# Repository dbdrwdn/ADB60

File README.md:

# ADB60

A modified [donegal-c](https://github.com/piit79/donegal-c).

This PCB allows to use the keycaps of an alphanumerical block of the Apple ADB keyboard as 60% keyboard.
It is designed to be used without any case.

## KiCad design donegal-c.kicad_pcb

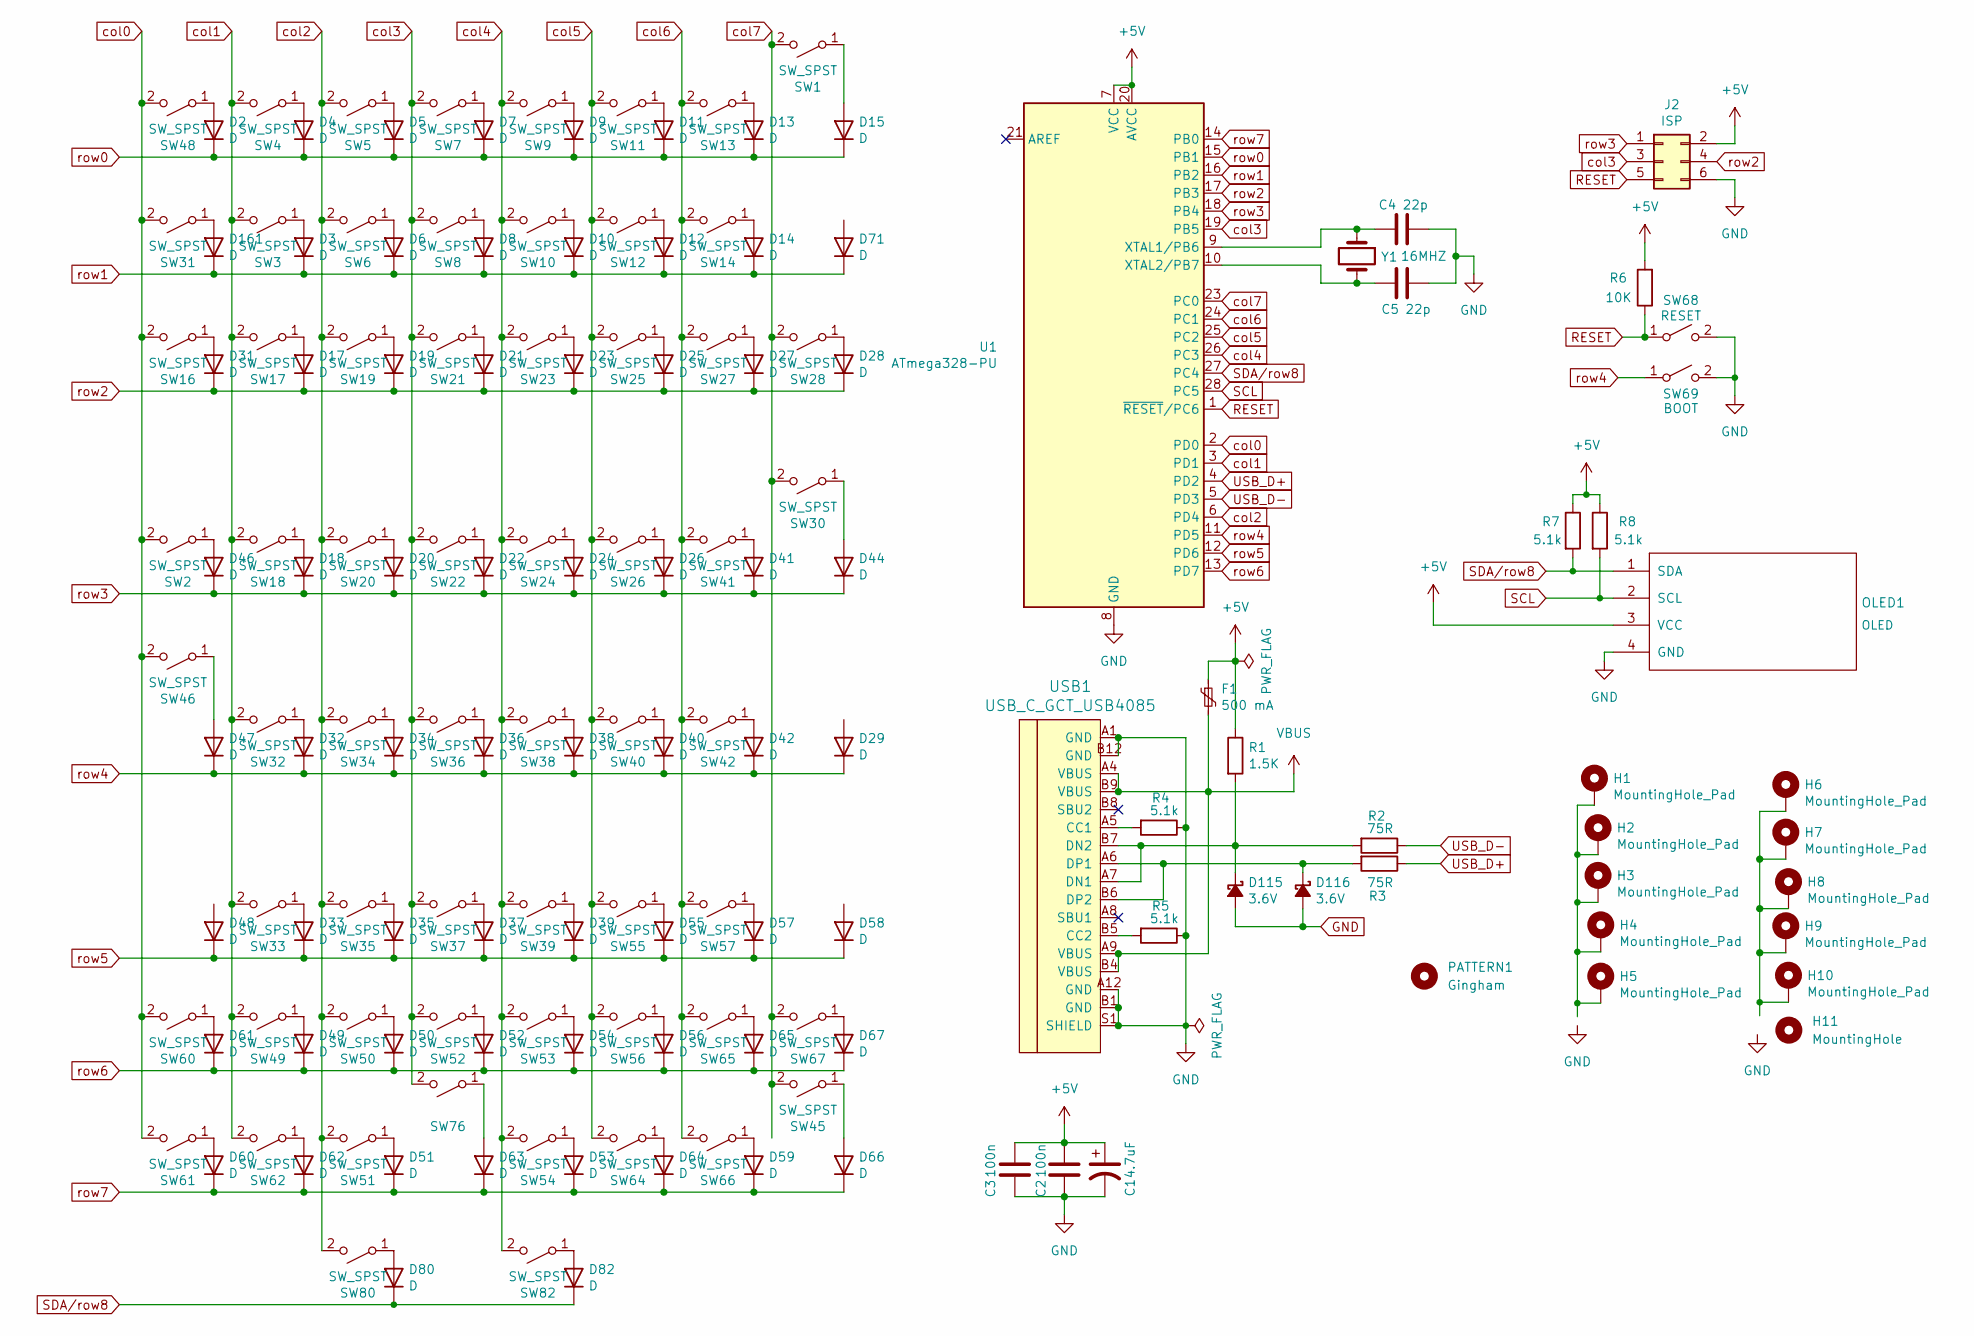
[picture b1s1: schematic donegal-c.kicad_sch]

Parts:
C1: 4.7uF; CP_Radial_D4.0mm_P1.50mm
C2, C3: 100n; C_Disc_D4.3mm_W1.9mm_P5.00mm
C4, C5: 22p; C_Disc_D3.0mm_W1.6mm_P2.50mm
D2, D3, D4, D5, D6, D7, D8, D9, D10, D11, D12, D13, D14, D15, D17, D18, D19, D20, D21, D22, D23, D24, D25, D26, D27, D28, D29, D31, D32, D33, D34, D35, D36, D37, D38, D39, D40, D41, D42, D44, D46, D47, D48, D49, D50, D51, D52, D53, D54, D55, D56, D57, D58, D59, D60, D61, D62, D63, D64, D65, D66, D67, D71, D80, D82, D161: D; D_DO-35_SOD27_P7.62mm_Horizontal
D115, D116: 3.6V; D_DO-35_SOD27_P7.62mm_Horizontal
F1: 500 mA; C_Disc_D5.0mm_W2.5mm_P5.00mm
H1, H2: MountingHole_Pad; MountingHole_2.2mm_M2
H3, H4, H6, H7, H8, H9, H10: MountingHole_Pad; MountingHole_2.2mm_M2_DIN965_Pad
H5: MountingHole_Pad; MountingHole_2.2mm_M2_DIN965
H11: MountingHole; MountingHole_2.2mm_M2
J2: ISP; PinHeader_2x03_P2.54mm_Vertical
OLED1: OLED; OLED_v2.1
PATTERN1: Gingham; gingham
R1: 1.5K; R_Axial_DIN0204_L3.6mm_D1.6mm_P5.08mm_Horizontal
R2, R3: 75R; R_Axial_DIN0204_L3.6mm_D1.6mm_P5.08mm_Horizontal
R4, R5, R7, R8: 5.1k; R_Axial_DIN0204_L3.6mm_D1.6mm_P5.08mm_Horizontal
R6: 10K; R_Axial_DIN0204_L3.6mm_D1.6mm_P5.08mm_Horizontal
SW1, SW16: SW_SPST; ALPS-1.5U
SW2, SW3, SW4, SW5, SW6, SW7, SW8, SW9, SW10, SW11, SW12, SW13, SW14, SW17, SW18, SW19, SW20, SW21, SW22, SW23, SW24, SW25, SW26, SW27, SW28, SW32, SW33, SW34, SW35, SW36, SW37, SW38, SW39, SW40, SW41, SW42, SW48, SW49, SW50, SW51, SW52, SW53, SW54, SW55, SW56, SW57, SW60, SW61, SW64, SW65, SW66, SW67, SW80, SW82: SW_SPST; ALPS-1U
SW30: SW_SPST; ALPS-2U
SW31, SW62: SW_SPST; ALPS-1.75U
SW45, SW46: SW_SPST; ALPS-2.25U
SW68: RESET; SW_PUSH_6mm
SW69: BOOT; SW_PUSH_6mm
SW76: (no value)
U1: ATmega328-PU; DIP-28_W7.62mm
USB1: USB_C_GCT_USB4085; USB_C_GCT_USB4085-offset-pads
Y1: 16MHZ; Crystal_HC49-4H_Vertical

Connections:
+5V: C1.1, C2.1, C3.1, F1.1, J2.2, OLED1.3 (VCC), R1.1, R6.2, R7.1, R8.1, U1.7 (VCC), U1.20 (AVCC)
GND: C1.2, C2.2, C3.2, C4.1, C5.1, D115.2 (A), D116.2 (A), J2.6, OLED1.4 (GND), R4.1, R5.1, SW68.2 (B), SW69.2 (B), U1.8 (GND), U1.22 (GND), USB1.A1 (GND), USB1.A12 (GND), USB1.B1 (GND), USB1.B12 (GND), USB1.S1 (SHIELD)
unnamed: C4.2, U1.9 (XTAL1/PB6), Y1.1
unnamed: C5.2, U1.10 (XTAL2/PB7), Y1.2
unnamed: D2.2 (A), SW48.1 (A)
unnamed: D3.2 (A), SW3.1 (A)
unnamed: D4.2 (A), SW4.1 (A)
unnamed: D5.2 (A), SW5.1 (A)
unnamed: D6.2 (A), SW6.1 (A)
unnamed: D7.2 (A), SW7.1 (A)
unnamed: D8.2 (A), SW8.1 (A)
unnamed: D9.2 (A), SW9.1 (A)
unnamed: D10.2 (A), SW10.1 (A)
unnamed: D11.2 (A), SW11.1 (A)
unnamed: D12.2 (A), SW12.1 (A)
unnamed: D13.2 (A), SW13.1 (A)
unnamed: D14.2 (A), SW14.1 (A)
unnamed: D15.2 (A), SW1.1 (A)
unnamed: D17.2 (A), SW17.1 (A)
unnamed: D18.2 (A), SW18.1 (A)
unnamed: D19.2 (A), SW19.1 (A)
unnamed: D20.2 (A), SW20.1 (A)
unnamed: D21.2 (A), SW21.1 (A)
unnamed: D22.2 (A), SW22.1 (A)
unnamed: D23.2 (A), SW23.1 (A)
unnamed: D24.2 (A), SW24.1 (A)
unnamed: D25.2 (A), SW25.1 (A)
unnamed: D26.2 (A), SW26.1 (A)
unnamed: D27.2 (A), SW27.1 (A)
unnamed: D28.2 (A), SW28.1 (A)
unnamed: D31.2 (A), SW16.1 (A)
unnamed: D32.2 (A), SW32.1 (A)
unnamed: D33.2 (A), SW33.1 (A)
unnamed: D34.2 (A), SW34.1 (A)
unnamed: D35.2 (A), SW35.1 (A)
unnamed: D36.2 (A), SW36.1 (A)
unnamed: D37.2 (A), SW37.1 (A)
unnamed: D38.2 (A), SW38.1 (A)
unnamed: D39.2 (A), SW39.1 (A)
unnamed: D40.2 (A), SW40.1 (A)
unnamed: D41.2 (A), SW41.1 (A)
unnamed: D42.2 (A), SW42.1 (A)
unnamed: D44.2 (A), SW30.1 (A)
unnamed: D46.2 (A), SW2.1 (A)
unnamed: D47.2 (A), SW46.1 (A)
unnamed: D49.2 (A), SW49.1 (A)
unnamed: D50.2 (A), SW50.1 (A)
unnamed: D51.2 (A), SW51.1 (A)
unnamed: D52.2 (A), SW52.1 (A)
unnamed: D53.2 (A), SW54.1 (A)
unnamed: D54.2 (A), SW53.1 (A)
unnamed: D55.2 (A), SW55.1 (A)
unnamed: D56.2 (A), SW56.1 (A)
unnamed: D57.2 (A), SW57.1 (A)
unnamed: D59.2 (A), SW66.1 (A)
unnamed: D60.2 (A), SW61.1 (A)
unnamed: D61.2 (A), SW60.1 (A)
unnamed: D62.2 (A), SW62.1 (A)
unnamed: D63.2 (A), SW76.1 (A)
unnamed: D64.2 (A), SW64.1 (A)
unnamed: D65.2 (A), SW65.1 (A)
unnamed: D66.2 (A), SW45.1 (A)
unnamed: D67.2 (A), SW67.1 (A)
unnamed: D80.2 (A), SW80.1 (A)
unnamed: D82.2 (A), SW82.1 (A)
unnamed: D115.1 (K), R1.2, R2.2, USB1.A7 (DN1), USB1.B7 (DN2)
unnamed: D116.1 (K), R3.2, USB1.A6 (DP1), USB1.B6 (DP2)
unnamed: D161.2 (A), SW31.1 (A)
unnamed: H1.1, H2.1, H3.1, H4.1, H5.1
unnamed: H6.1, H7.1, H8.1, H9.1, H10.1
unnamed: R4.2, USB1.A5 (CC1)
unnamed: R5.2, USB1.B5 (CC2)
RESET: J2.5, R6.1, SW68.1 (A), U1.1 (~RESET/PC6)
SCL: OLED1.2 (SCL), R8.2, U1.28 (PC5)
SDA/row8: D80.1 (K), D82.1 (K), OLED1.1 (SDA), R7.2, U1.27 (PC4)
USB_D+: R3.1, U1.4 (PD2)
USB_D-: R2.1, U1.5 (PD3)
VBUS: F1.2, USB1.A4 (VBUS), USB1.A9 (VBUS), USB1.B4 (VBUS), USB1.B9 (VBUS)
col0: SW2.2 (B), SW16.2 (B), SW31.2 (B), SW46.2 (B), SW48.2 (B), SW60.2 (B), SW61.2 (B), U1.2 (PD0)
col1: SW3.2 (B), SW4.2 (B), SW17.2 (B), SW18.2 (B), SW32.2 (B), SW33.2 (B), SW49.2 (B), SW62.2 (B), U1.3 (PD1)
col2: SW5.2 (B), SW6.2 (B), SW19.2 (B), SW20.2 (B), SW34.2 (B), SW35.2 (B), SW50.2 (B), SW51.2 (B), SW80.2 (B), U1.6 (PD4)
col3: J2.3, SW7.2 (B), SW8.2 (B), SW21.2 (B), SW22.2 (B), SW36.2 (B), SW37.2 (B), SW52.2 (B), SW76.2 (B), U1.19 (PB5)
col4: SW9.2 (B), SW10.2 (B), SW23.2 (B), SW24.2 (B), SW38.2 (B), SW39.2 (B), SW53.2 (B), SW54.2 (B), SW82.2 (B), U1.26 (PC3)
col5: SW11.2 (B), SW12.2 (B), SW25.2 (B), SW26.2 (B), SW40.2 (B), SW55.2 (B), SW56.2 (B), SW64.2 (B), U1.25 (PC2)
col6: SW13.2 (B), SW14.2 (B), SW27.2 (B), SW41.2 (B), SW42.2 (B), SW57.2 (B), SW65.2 (B), SW66.2 (B), U1.24 (PC1)
col7: SW1.2 (B), SW28.2 (B), SW30.2 (B), SW45.2 (B), SW67.2 (B), U1.23 (PC0)
row0: D2.1 (K), D4.1 (K), D5.1 (K), D7.1 (K), D9.1 (K), D11.1 (K), D13.1 (K), D15.1 (K), U1.15 (PB1)
row1: D3.1 (K), D6.1 (K), D8.1 (K), D10.1 (K), D12.1 (K), D14.1 (K), D71.1 (K), D161.1 (K), U1.16 (PB2)
row2: D17.1 (K), D19.1 (K), D21.1 (K), D23.1 (K), D25.1 (K), D27.1 (K), D28.1 (K), D31.1 (K), J2.4, U1.17 (PB3)
row3: D18.1 (K), D20.1 (K), D22.1 (K), D24.1 (K), D26.1 (K), D41.1 (K), D44.1 (K), D46.1 (K), J2.1, U1.18 (PB4)
row4: D29.1 (K), D32.1 (K), D34.1 (K), D36.1 (K), D38.1 (K), D40.1 (K), D42.1 (K), D47.1 (K), SW69.1 (A), U1.11 (PD5)
row5: D33.1 (K), D35.1 (K), D37.1 (K), D39.1 (K), D48.1 (K), D55.1 (K), D57.1 (K), D58.1 (K), U1.12 (PD6)
row6: D49.1 (K), D50.1 (K), D52.1 (K), D54.1 (K), D56.1 (K), D61.1 (K), D65.1 (K), D67.1 (K), U1.13 (PD7)
row7: D51.1 (K), D53.1 (K), D59.1 (K), D60.1 (K), D62.1 (K), D63.1 (K), D64.1 (K), D66.1 (K), U1.14 (PB0)

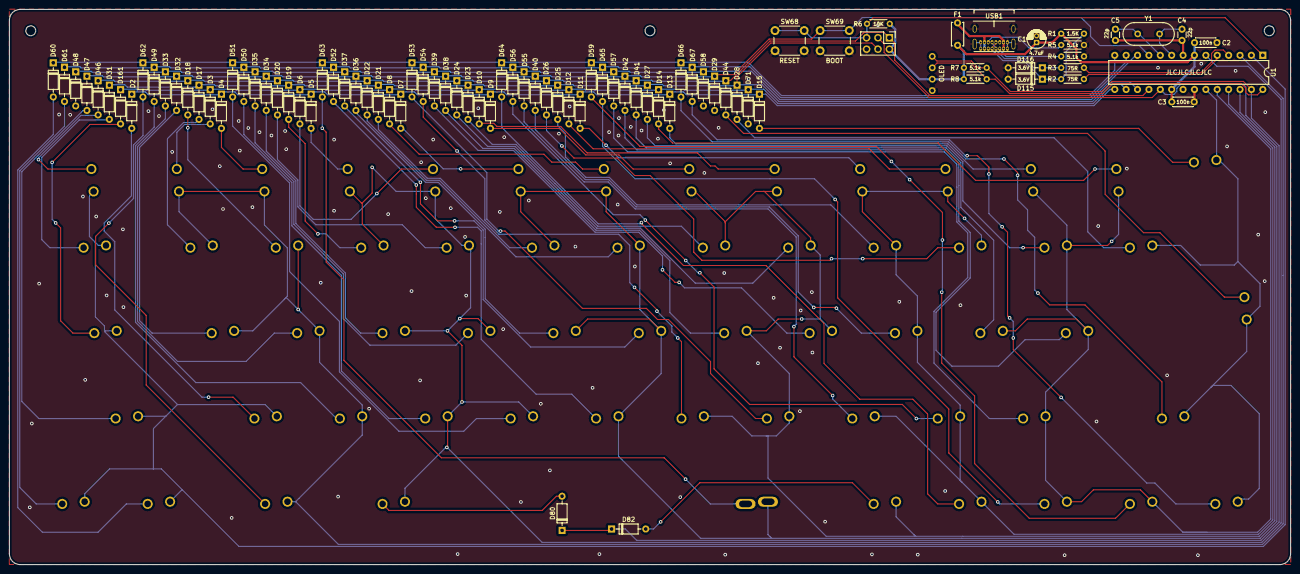
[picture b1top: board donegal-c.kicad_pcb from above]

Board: 2 copper layers, 285.8 x 123.8 mm, 154 parts (0 on the bottom side), 92 nets.

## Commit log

2021-01-16 Replace ZIPs with actual KiCad projects/QMK source and rename to Donegal-C
2021-01-16 Replace Mini USB with USB-C; reroute top and cleanup
2021-01-18 Use MX-only switch footprints
2021-08-12 Add component values to the silk screen
2021-08-12 Remove QMK code
2022-08-24 Rename and set correct remote for the MX_Alps_Hybrid library
2022-08-25 Add 42. Keebs KiCad library as a submodule
2022-08-25 Update to v1.2
    * Add Tsangan bottom row support
    * Switch to MX_Alps_Hybrid MX_Only switch footprints
    * Re-add the indicator LED to schematic
2022-08-25 Remove unneeded footprints from the local tartan library
2022-08-25 Remove unused library/submodule random-keyboard-parts
2022-08-25 Update 42. Keebs KiCad library
2022-08-25 Use USB-C socket symbol from the 42. Keebs library
2022-08-25 Remove unused local symbol library donegal-c
2022-08-25 Fix incorrect bottom row sizes; add bottom row key labels
2022-08-26 Add labels for ANSI/ISO keys
2022-08-28 Update the 42. Keebs KiCad library
2022-08-28 Add support for optional OLED (I/O shared with split bottom row)
2022-11-11 Add gerber directory to .gitignore
2022-11-11 Minor improvements in component positions
2022-11-11 Remove exclusion zones under the crystal
2022-12-07 Exclude inevitable DRC violations
2022-12-07 Add switch plate and bottom plate files
2022-12-07 Add acrylic cover, plate and foam files
2022-12-07 Update README, add PCB render
2023-01-15 initial change to readme
2023-01-15 removed unneeded files and replaced others
2023-01-15 remove .DS_Store
2023-01-15 removed pattern and text from silkscreen
2023-01-15 changed spacebar to wider hole and moved some silk
2023-01-15 added JLCJLCJLCJLC to place order number under MCU
2023-03-05 first steps to remove all silk
2023-03-05 rework by jakob
